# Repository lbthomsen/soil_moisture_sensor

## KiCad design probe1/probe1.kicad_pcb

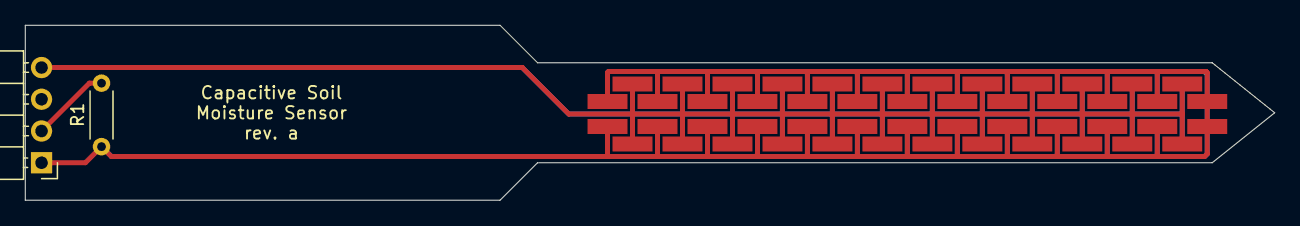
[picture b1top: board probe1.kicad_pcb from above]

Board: 2 copper layers, 100.0 x 14.0 mm, 4 parts (1 on the bottom side), 3 nets.

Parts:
C1, C2: Soil Sensor; soil_sensor_no_trace
J1: PinHeader_1x04_P2.54mm_Horizontal
R1: NM; R_Axial_DIN0204_L3.6mm_D1.6mm_P5.08mm_Horizontal

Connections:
GND: C1.2, C2.2, J1.4
unnamed: C1.1, C2.1, J1.1, R1.1
unnamed: J1.2, R1.2

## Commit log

2021-11-18 Hmmm
2021-11-23 Hmmmm
